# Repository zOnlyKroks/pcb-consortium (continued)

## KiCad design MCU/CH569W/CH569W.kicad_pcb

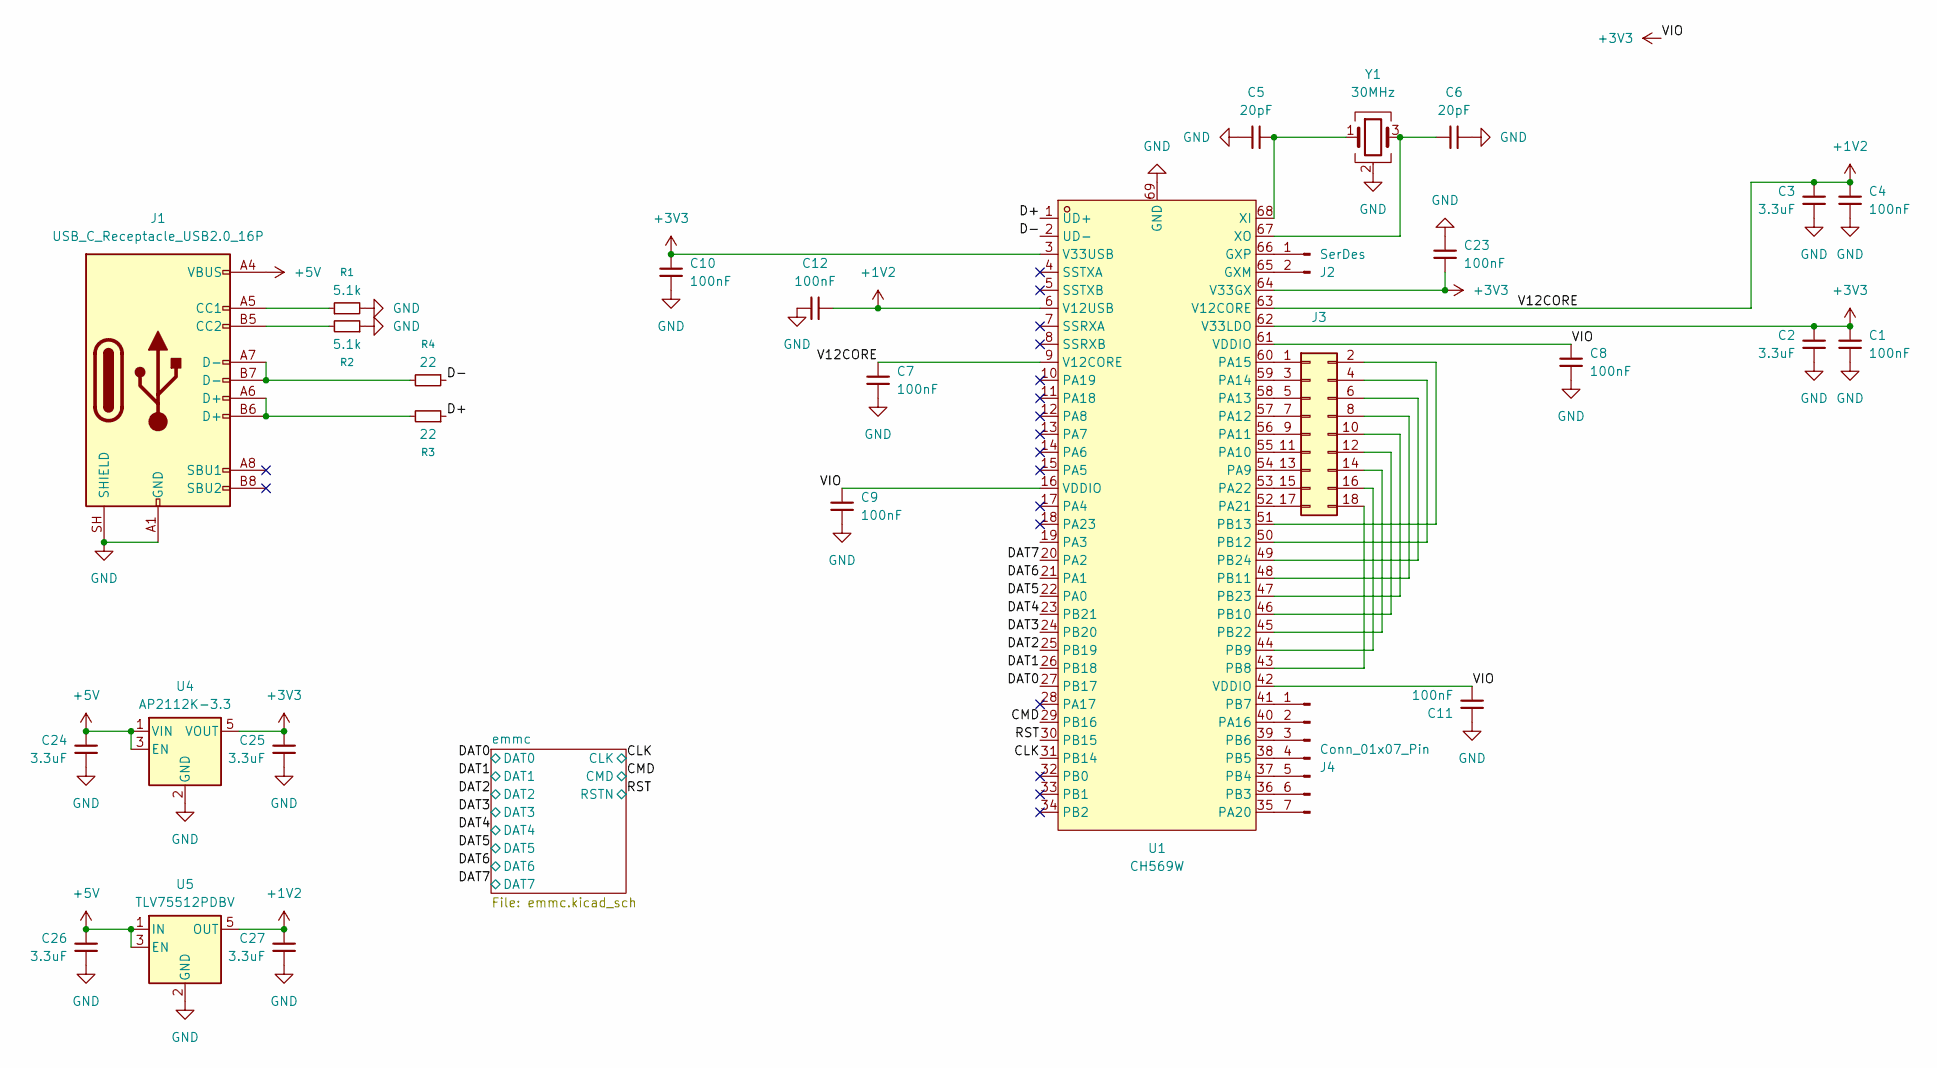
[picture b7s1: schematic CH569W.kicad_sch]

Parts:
C1, C4, C7, C8, C9, C10, C11, C12, C23: 100nF; C_0603_1608Metric
C2, C3, C24, C25, C26, C27: 3.3uF; C_0603_1608Metric
C5, C6: 20pF; C_0603_1608Metric
J1: USB_C_Receptacle_USB2.0_16P; USB_C_Receptacle_HRO_TYPE-C-31-M-12
J2: SerDes; PinHeader_1x02_P2.54mm_Vertical
J3: Conn_02x09_Odd_Even; PinHeader_2x09_P2.54mm_Vertical
J4: Conn_01x07_Pin; PinHeader_1x07_P2.54mm_Vertical
R1, R2: 5.1k; R_0603_1608Metric
R3, R4: 22; R_0603_1608Metric
U1: CH569W; MPN CH569W; LCSC Part C2857462
U4: AP2112K-3.3; SOT-23-5
U5: TLV75512PDBV; SOT-23-5
Y1: 30MHz; Crystal_SMD_3225-4Pin_3.2x2.5mm

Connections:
+1V2: C3.1, C4.1, C7.1, C12.2, C27.1, U1.6 (V12USB), U1.9 (V12CORE), U1.63 (V12CORE), U5.5 (OUT)
+3V3: C1.1, C2.1, C8.1, C9.1, C10.1, C11.2, C23.2, C25.1, U1.3 (V33USB), U1.16 (VDDIO), U1.42 (VDDIO), U1.61 (VDDIO), U1.62 (V33LDO), U1.64 (V33GX), U4.5 (VOUT); also elsewhere on the board
+5V: C24.1, C26.1, J1.A4 (VBUS), J1.A9 (VBUS), J1.B4 (VBUS), J1.B9 (VBUS), U4.1 (VIN), U4.3 (EN), U5.1 (IN), U5.3 (EN)
/CLK: U1.31 (PB14); also elsewhere on the board
/CMD: U1.29 (PB16); also elsewhere on the board
/D+: R3.1, U1.1 (UD+)
/D-: R4.1, U1.2 (UD-)
/DAT0: U1.27 (PB17); also elsewhere on the board
/DAT1: U1.26 (PB18); also elsewhere on the board
/DAT2: U1.25 (PB19); also elsewhere on the board
/DAT3: U1.24 (PB20); also elsewhere on the board
/DAT4: U1.23 (PB21); also elsewhere on the board
/DAT5: U1.22 (PA0); also elsewhere on the board
/DAT6: U1.21 (PA1); also elsewhere on the board
/DAT7: U1.20 (PA2); also elsewhere on the board
/RST: U1.30 (PB15); also elsewhere on the board
GND: C1.2, C2.2, C3.2, C4.2, C5.1, C6.2, C7.2, C8.2, C9.2, C10.2, C11.1, C12.1, C23.1, C24.2, C25.2, C26.2, C27.2, J1.A1 (GND), J1.A12 (GND), J1.B1 (GND), J1.B12 (GND), J1.SH (SHIELD), R1.2, R2.1, U1.69 (GND), U4.2 (GND), U5.2 (GND), Y1.2 (G), Y1.4 (G); also elsewhere on the board
unnamed: J1.A5 (CC1), R1.1
unnamed: J1.B5 (CC2), R2.2
unnamed: J1.A6 (D+), J1.B6 (D+), R3.2
unnamed: J1.A7 (D-), J1.B7 (D-), R4.2
unnamed: J2.1, U1.66 (GXP)
unnamed: J2.2, U1.65 (GXM)
unnamed: J3.1, U1.60 (PA15)
unnamed: J3.2, U1.51 (PB13)
unnamed: J3.3, U1.59 (PA14)
unnamed: J3.4, U1.50 (PB12)
unnamed: J3.5, U1.58 (PA13)
unnamed: J3.6, U1.49 (PB24)
unnamed: J3.7, U1.57 (PA12)
unnamed: J3.8, U1.48 (PB11)
unnamed: J3.9, U1.56 (PA11)
unnamed: J3.10, U1.47 (PB23)
unnamed: J3.11, U1.55 (PA10)
unnamed: J3.12, U1.46 (PB10)
unnamed: J3.13, U1.54 (PA9)
unnamed: J3.14, U1.45 (PB22)
unnamed: J3.15, U1.53 (PA22)
unnamed: J3.16, U1.44 (PB9)
unnamed: J3.17, U1.52 (PA21)
unnamed: J3.18, U1.43 (PB8)
unnamed: J4.1, U1.41 (PB7)
unnamed: J4.2, U1.40 (PA16)
unnamed: J4.3, U1.39 (PB6)
unnamed: J4.4, U1.38 (PB5)
unnamed: J4.5, U1.37 (PB4)
unnamed: J4.6, U1.36 (PB3)
unnamed: J4.7, U1.35 (PA20)
unnamed: C5.2, U1.68 (XI), Y1.1
unnamed: C6.1, U1.67 (XO), Y1.3

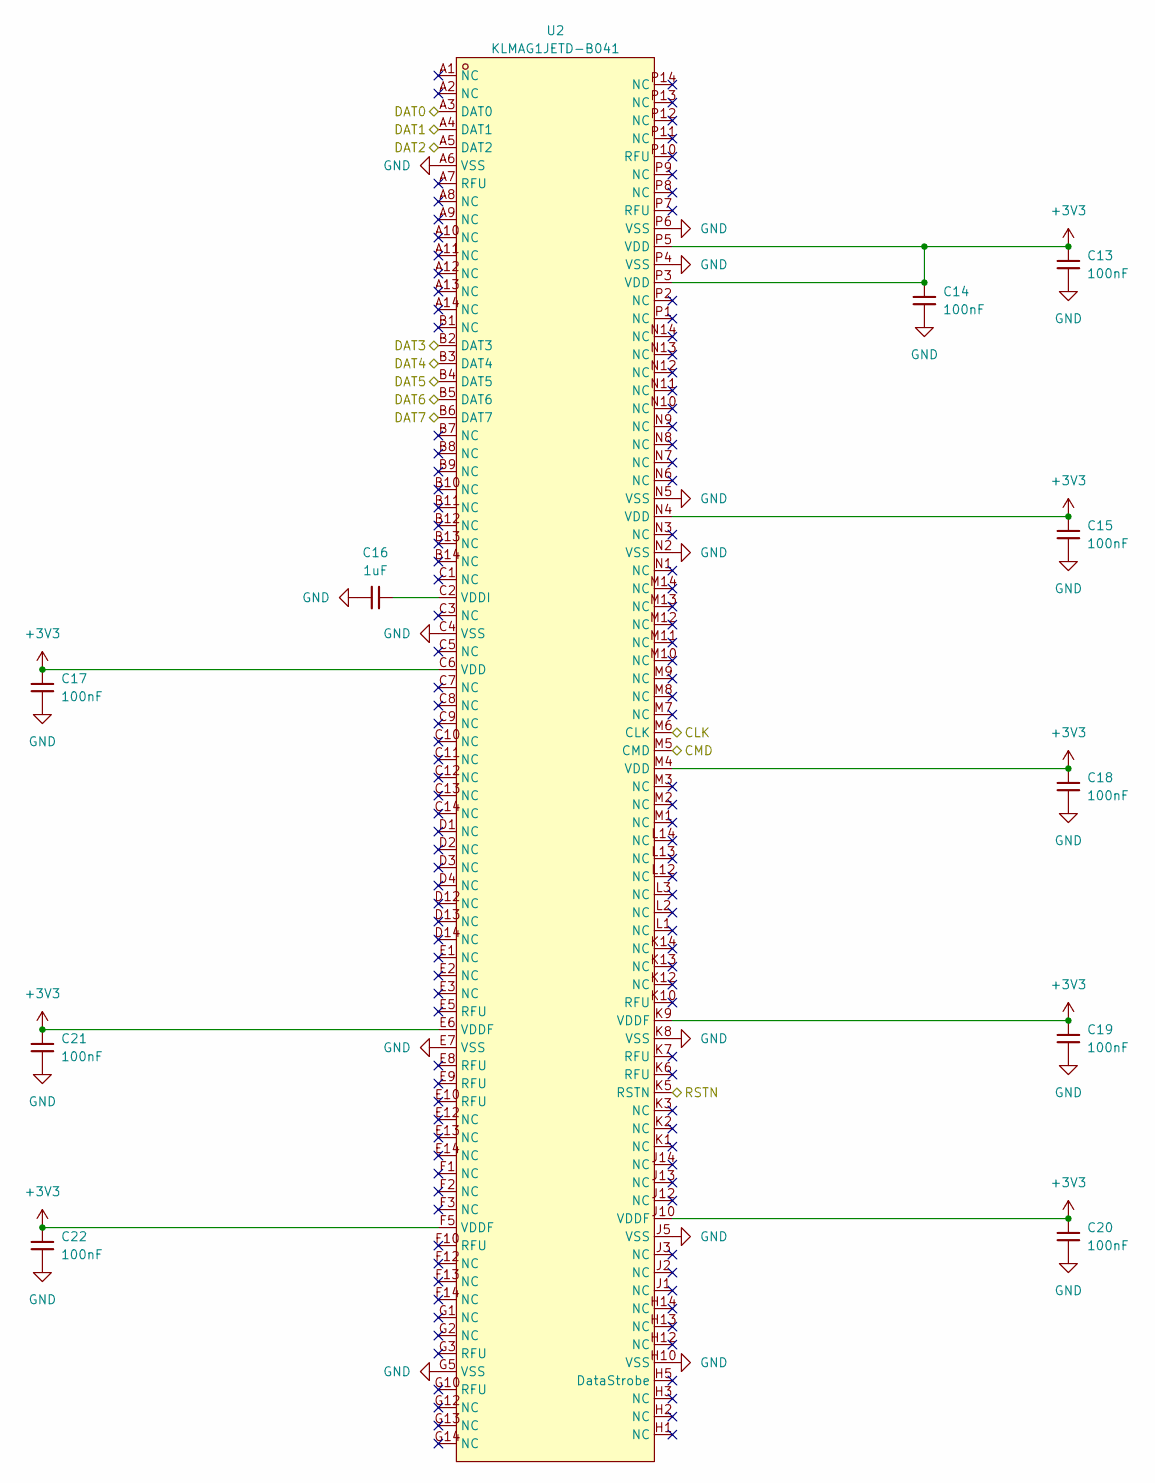
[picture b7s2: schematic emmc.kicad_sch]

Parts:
C13, C14, C15, C17, C18, C19, C20, C21, C22: 100nF; C_0603_1608Metric
C16: 1uF; C_0603_1608Metric
U2: KLMAG1JETD-B041; MPN KLMAG1JETD-B041; LCSC Part C499919

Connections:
+3V3: C13.1, C14.1, C15.1, C17.1, C18.1, C19.1, C20.1, C21.1, C22.1, U2.C6 (VDD), U2.E6 (VDDF), U2.F5 (VDDF), U2.J10 (VDDF), U2.K9 (VDDF), U2.M4 (VDD), U2.N4 (VDD), U2.P3 (VDD), U2.P5 (VDD); also elsewhere on the board
/CLK: U2.M6 (CLK); also elsewhere on the board
/CMD: U2.M5 (CMD); also elsewhere on the board
/DAT0: U2.A3 (DAT0); also elsewhere on the board
/DAT1: U2.A4 (DAT1); also elsewhere on the board
/DAT2: U2.A5 (DAT2); also elsewhere on the board
/DAT3: U2.B2 (DAT3); also elsewhere on the board
/DAT4: U2.B3 (DAT4); also elsewhere on the board
/DAT5: U2.B4 (DAT5); also elsewhere on the board
/DAT6: U2.B5 (DAT6); also elsewhere on the board
/DAT7: U2.B6 (DAT7); also elsewhere on the board
/RST: U2.K5 (RSTN); also elsewhere on the board
GND: C13.2, C14.2, C15.2, C16.1, C17.2, C18.2, C19.2, C20.2, C21.2, C22.2, U2.A6 (VSS), U2.C4 (VSS), U2.E7 (VSS), U2.G5 (VSS), U2.H10 (VSS), U2.J5 (VSS), U2.K8 (VSS), U2.N2 (VSS), U2.N5 (VSS), U2.P4 (VSS), U2.P6 (VSS); also elsewhere on the board
unnamed: C16.2, U2.C2 (VDDI)

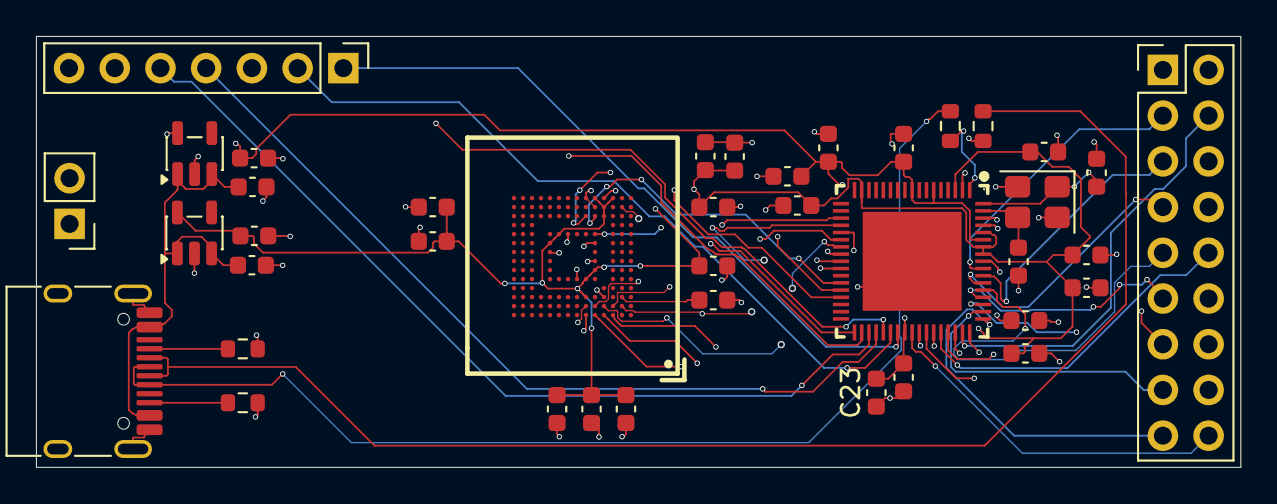
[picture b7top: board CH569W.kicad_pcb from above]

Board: 4 copper layers, 66.9 x 23.9 mm, 40 parts (0 on the bottom side), 51 nets.

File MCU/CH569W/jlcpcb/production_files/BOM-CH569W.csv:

Comment,Designator,Footprint,LCSC,Quantity
CH569W,U1,CH569W,C2857462,1
KLMAG1JETD-B041,U2,KLMAG1JETD-B041,C499919,1
5.1k,R2,R_0603_1608Metric,,1
3.3uF,C3,C_0603_1608Metric,,1
3.3uF,C2,C_0603_1608Metric,,1
100nF,C21,C_0603_1608Metric,,1
USB_C_Receptacle_USB2.0_16P,J1,USB_C_Receptacle_HRO_TYPE-C-31-M-12,,1
20pF,C6,C_0603_1608Metric,,1
20pF,C5,C_0603_1608Metric,,1
Conn_02x09_Odd_Even,J3,PinHeader_2x09_P2.54mm_Vertical,,1
100nF,C23,C_0603_1608Metric,,1
100nF,C22,C_0603_1608Metric,,1
Conn_01x07_Pin,J4,PinHeader_1x07_P2.54mm_Vertical,,1
100nF,C7,C_0603_1608Metric,,1
100nF,C9,C_0603_1608Metric,,1
100nF,C4,C_0603_1608Metric,,1
100nF,C13,C_0603_1608Metric,,1
30MHz,Y1,Crystal_SMD_3225-4Pin_3.2x2.5mm,,1
100nF,C14,C_0603_1608Metric,,1
22,R4,R_0603_1608Metric,,1
3.3uF,C25,C_0603_1608Metric,,1
100nF,C12,C_0603_1608Metric,,1
AP2112K-3.3,U4,SOT-23-5,,1
3.3uF,C24,C_0603_1608Metric,,1
3.3uF,C27,C_0603_1608Metric,,1
100nF,C20,C_0603_1608Metric,,1
100nF,C10,C_0603_1608Metric,,1
1uF,C16,C_0603_1608Metric,,1
22,R3,R_0603_1608Metric,,1
100nF,C19,C_0603_1608Metric,,1
100nF,C17,C_0603_1608Metric,,1
100nF,C18,C_0603_1608Metric,,1
100nF,C8,C_0603_1608Metric,,1
TLV75512PDBV,U5,SOT-23-5,,1
100nF,C1,C_0603_1608Metric,,1
5.1k,R1,R_0603_1608Metric,,1
3.3uF,C26,C_0603_1608Metric,,1
SerDes,J2,PinHeader_1x02_P2.54mm_Vertical,,1
100nF,C11,C_0603_1608Metric,,1
100nF,C15,C_0603_1608Metric,,1

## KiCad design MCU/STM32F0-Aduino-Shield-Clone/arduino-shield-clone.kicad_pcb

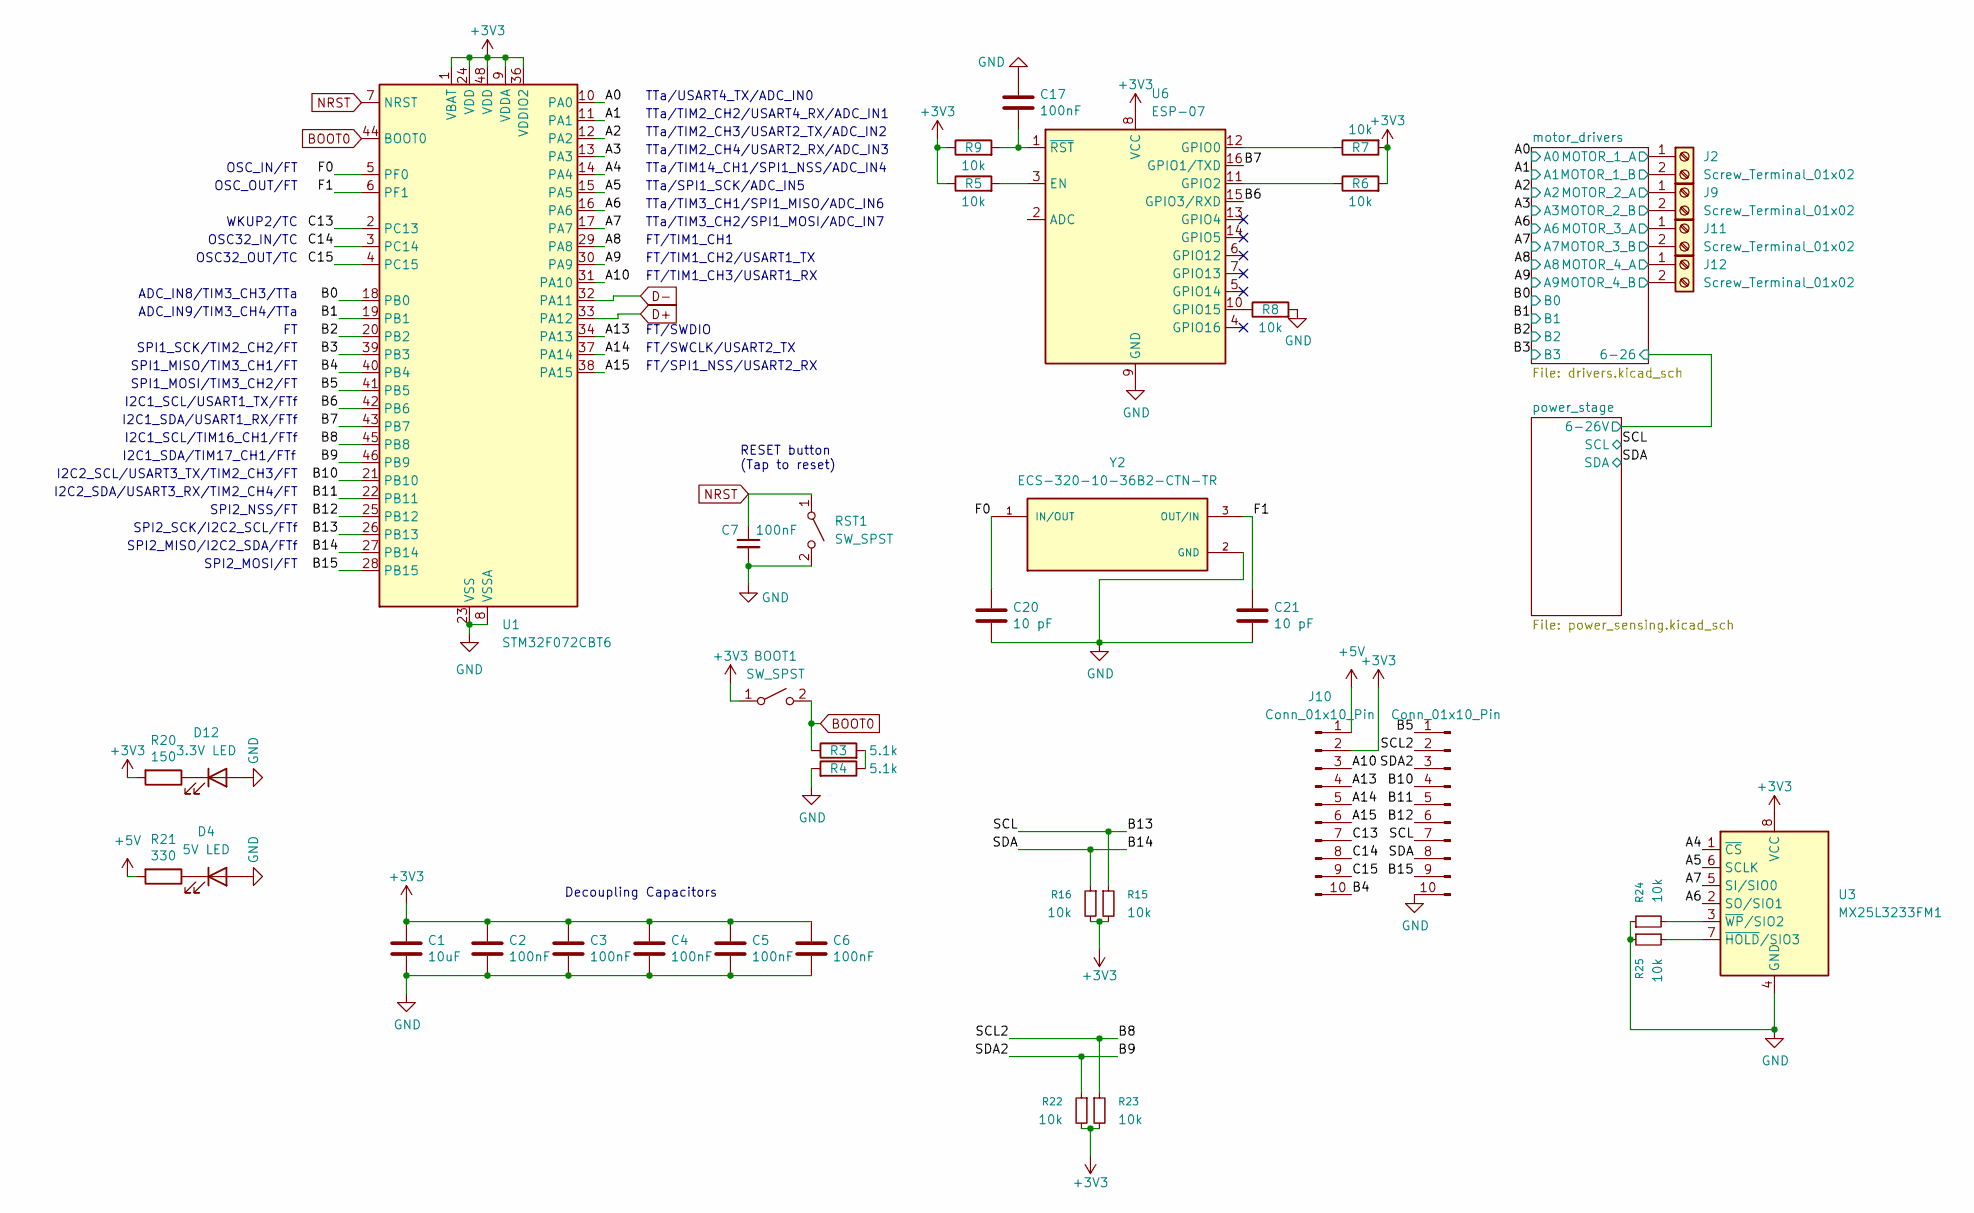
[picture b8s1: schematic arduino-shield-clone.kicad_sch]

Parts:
BOOT1: SW_SPST; SW_SPST_TL3342; LCSC Part # C2886897
C1: 10uF; C_0805_2012Metric; LCSC C307331
C2, C3, C4, C5, C6, C7, C17: 100nF; C_0805_2012Metric; LCSC C307331
C20, C21: 10 pF; C_0805_2012Metric; LCSC C307331
D4: 5V LED; LED_0805_2012Metric; LCSC Part # C98225
D12: 3.3V LED; LED_0805_2012Metric; LCSC Part # C98225
J2, J9, J11, J12: Screw_Terminal_01x02; TerminalBlock_Phoenix_MKDS-1,5-2-5.08_1x02_P5.08mm_Horizont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; LCSC Part # C5183929
J8, J10: Conn_01x10_Pin; PinHeader_1x10_P2.54mm_Vertical; LCSC Part # C42431810
R3, R4: 5.1k; R_0805_2012Metric
R5, R6, R7, R8, R9, R15, R16, R22, R23, R24, R25: 10k; R_0805_2012Metric; LCSC Part # C84376
R20: 150; R_0805_2012Metric; LCSC Part # C17471
R21: 330; R_0805_2012Metric; LCSC Part # C17630
RST1: SW_SPST; SW_SPST_TL3342; LCSC Part # C2886897
U1: STM32F072CBT6; LQFP-48_7x7mm_P0.5mm; JlcRotOffset 90
U3: MX25L3233FM1; JEITA_SOIC-8_3.9x4.9mm_P1.27mm; LCSC Part # C2802994
U6: ESP-07; LCSC Part # C82894
Y2: ECS-320-10-36B2-CTN-TR; XTAL_ECS-320-10-36B2-CTN-TR; PARTREV 2018; LCSC Part # C6239260

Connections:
+3V3: BOOT1.1 (A), C1.1, C2.1, C3.1, C4.1, C5.1, C6.1, J10.2, R5.1, R6.2, R7.2, R9.1, R15.2, R16.2, R20.2, R22.2, R23.2, U1.1 (VBAT), U1.9 (VDDA), U1.24 (VDD), U1.36 (VDDIO2), U1.48 (VDD), U3.8 (VCC), U6.8 (VCC); also elsewhere on the board
+5V: J10.1, R21.2; also elsewhere on the board
/A0: U1.10 (PA0); also elsewhere on the board
/A1: U1.11 (PA1); also elsewhere on the board
/A2: U1.12 (PA2); also elsewhere on the board
/A3: U1.13 (PA3); also elsewhere on the board
/A4: U1.14 (PA4), U3.1 (~CS)
/A5: U1.15 (PA5), U3.6 (SCLK)
/A6: U1.16 (PA6), U3.2 (SO/SIO1); also elsewhere on the board
/A7: U1.17 (PA7), U3.5 (SI/SIO0); also elsewhere on the board
/A8: U1.29 (PA8); also elsewhere on the board
/A9: U1.30 (PA9); also elsewhere on the board
/A10: J10.3, U1.31 (PA10)
/A13: J10.4, U1.34 (PA13)
/A14: J10.5, U1.37 (PA14)
/A15: J10.6, U1.38 (PA15)
/B0: U1.18 (PB0); also elsewhere on the board
/B1: U1.19 (PB1); also elsewhere on the board
/B2: U1.20 (PB2); also elsewhere on the board
/B3: U1.39 (PB3); also elsewhere on the board
/B4: J10.10, U1.40 (PB4)
/B5: J8.1, U1.41 (PB5)
/B6: U1.42 (PB6), U6.15 (GPIO3/RXD)
/B7: U1.43 (PB7), U6.16 (GPIO1/TXD)
/B8: J8.2, R23.1, U1.45 (PB8)
/B9: J8.3, R22.1, U1.46 (PB9)
/B10: J8.4, U1.21 (PB10)
/B11: J8.5, U1.22 (PB11)
/B12: J8.6, U1.25 (PB12)
/B13: J8.7, R15.1, U1.26 (PB13)
/B14: J8.8, R16.1, U1.27 (PB14)
/B15: J8.9, U1.28 (PB15)
/C13: J10.7, U1.2 (PC13)
/C14: J10.8, U1.3 (PC14)
/C15: J10.9, U1.4 (PC15)
/F0: C20.1, U1.5 (PF0), Y2.1 (IN/OUT)
/F1: C21.1, U1.6 (PF1), Y2.3 (OUT/IN)
/motor_drivers/MOTOR_1_A: J2.1; also elsewhere on the board
/motor_drivers/MOTOR_1_B: J2.2; also elsewhere on the board
/motor_drivers/MOTOR_2_A: J9.1; also elsewhere on the board
/motor_drivers/MOTOR_2_B: J9.2; also elsewhere on the board
/motor_drivers/MOTOR_3_A: J11.1; also elsewhere on the board
/motor_drivers/MOTOR_3_B: J11.2; also elsewhere on the board
/motor_drivers/MOTOR_4_A: J12.1; also elsewhere on the board
/motor_drivers/MOTOR_4_B: J12.2; also elsewhere on the board
BOOT0: BOOT1.2 (B), R3.1, U1.44 (BOOT0)
D+: U1.33 (PA12); also elsewhere on the board
D-: U1.32 (PA11); also elsewhere on the board
GND: C1.2, C2.2, C3.2, C4.2, C5.2, C6.2, C7.2, C17.1, C20.2, C21.2, D4.2 (A), D12.2 (A), J8.10, R4.2, R8.2, R24.1, R25.1, RST1.2 (B), U1.8 (VSSA), U1.23 (VSS), U1.35 (VSS), U1.47 (VSS), U3.4 (GND), U6.9 (GND), Y2.2 (GND), Y2.4 (GND); also elsewhere on the board
NRST: C7.1, RST1.1 (A), U1.7 (NRST)
unnamed: D4.1 (K), R21.1
unnamed: D12.1 (K), R20.1
unnamed: R3.2, R4.1
unnamed: R25.2, U3.7 (~HOLD/SIO3)
unnamed: R24.2, U3.3 (~WP/SIO2)
unnamed: R5.2, U6.3 (EN)
unnamed: R7.1, U6.12 (GPIO0)
unnamed: R6.1, U6.11 (GPIO2)
unnamed: R8.1, U6.10 (GPIO15)
unnamed: C17.2, R9.2, U6.1 (~RST)

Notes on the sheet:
TTa/TIM14_CH1/SPI1_NSS/ADC_IN4
ADC_IN8/TIM3_CH3/TTa
FT/SWCLK/USART2_TX
Decoupling Capacitors
FT/TIM1_CH2/USART1_TX
TTa/USART4_TX/ADC_IN0
TTa/TIM3_CH2/SPI1_MOSI/ADC_IN7
TTa/TIM2_CH3/USART2_TX/ADC_IN2
FT/SPI1_NSS/USART2_RX
I2C1_SCL/TIM16_CH1/FTf
SPI1_MOSI/TIM3_CH2/FT
SPI1_SCK/TIM2_CH2/FT
WKUP2/TC
SPI2_MOSI/FT
RESET button (Tap to reset)
OSC32_IN/TC
FT/TIM1_CH3/USART1_RX
I2C1_SCL/USART1_TX/FTf
TTa/TIM2_CH2/USART4_RX/ADC_IN1
TTa/TIM2_CH4/USART2_RX/ADC_IN3
TTa/SPI1_SCK/ADC_IN5
ADC_IN9/TIM3_CH4/TTa
I2C2_SCL/USART3_TX/TIM2_CH3/FT
I2C1_SDA/TIM17_CH1/FTf
SPI2_NSS/FT
SPI1_MISO/TIM3_CH1/FT
TTa/TIM3_CH1/SPI1_MISO/ADC_IN6
OSC_IN/FT
OSC_OUT/FT
OSC32_OUT/TC
FT/TIM1_CH1
SPI2_SCK/I2C2_SCL/FTf
I2C1_SDA/USART1_RX/FTf
I2C2_SDA/USART3_RX/TIM2_CH4/FT
FT/SWDIO
SPI2_MISO/I2C2_SDA/FTf

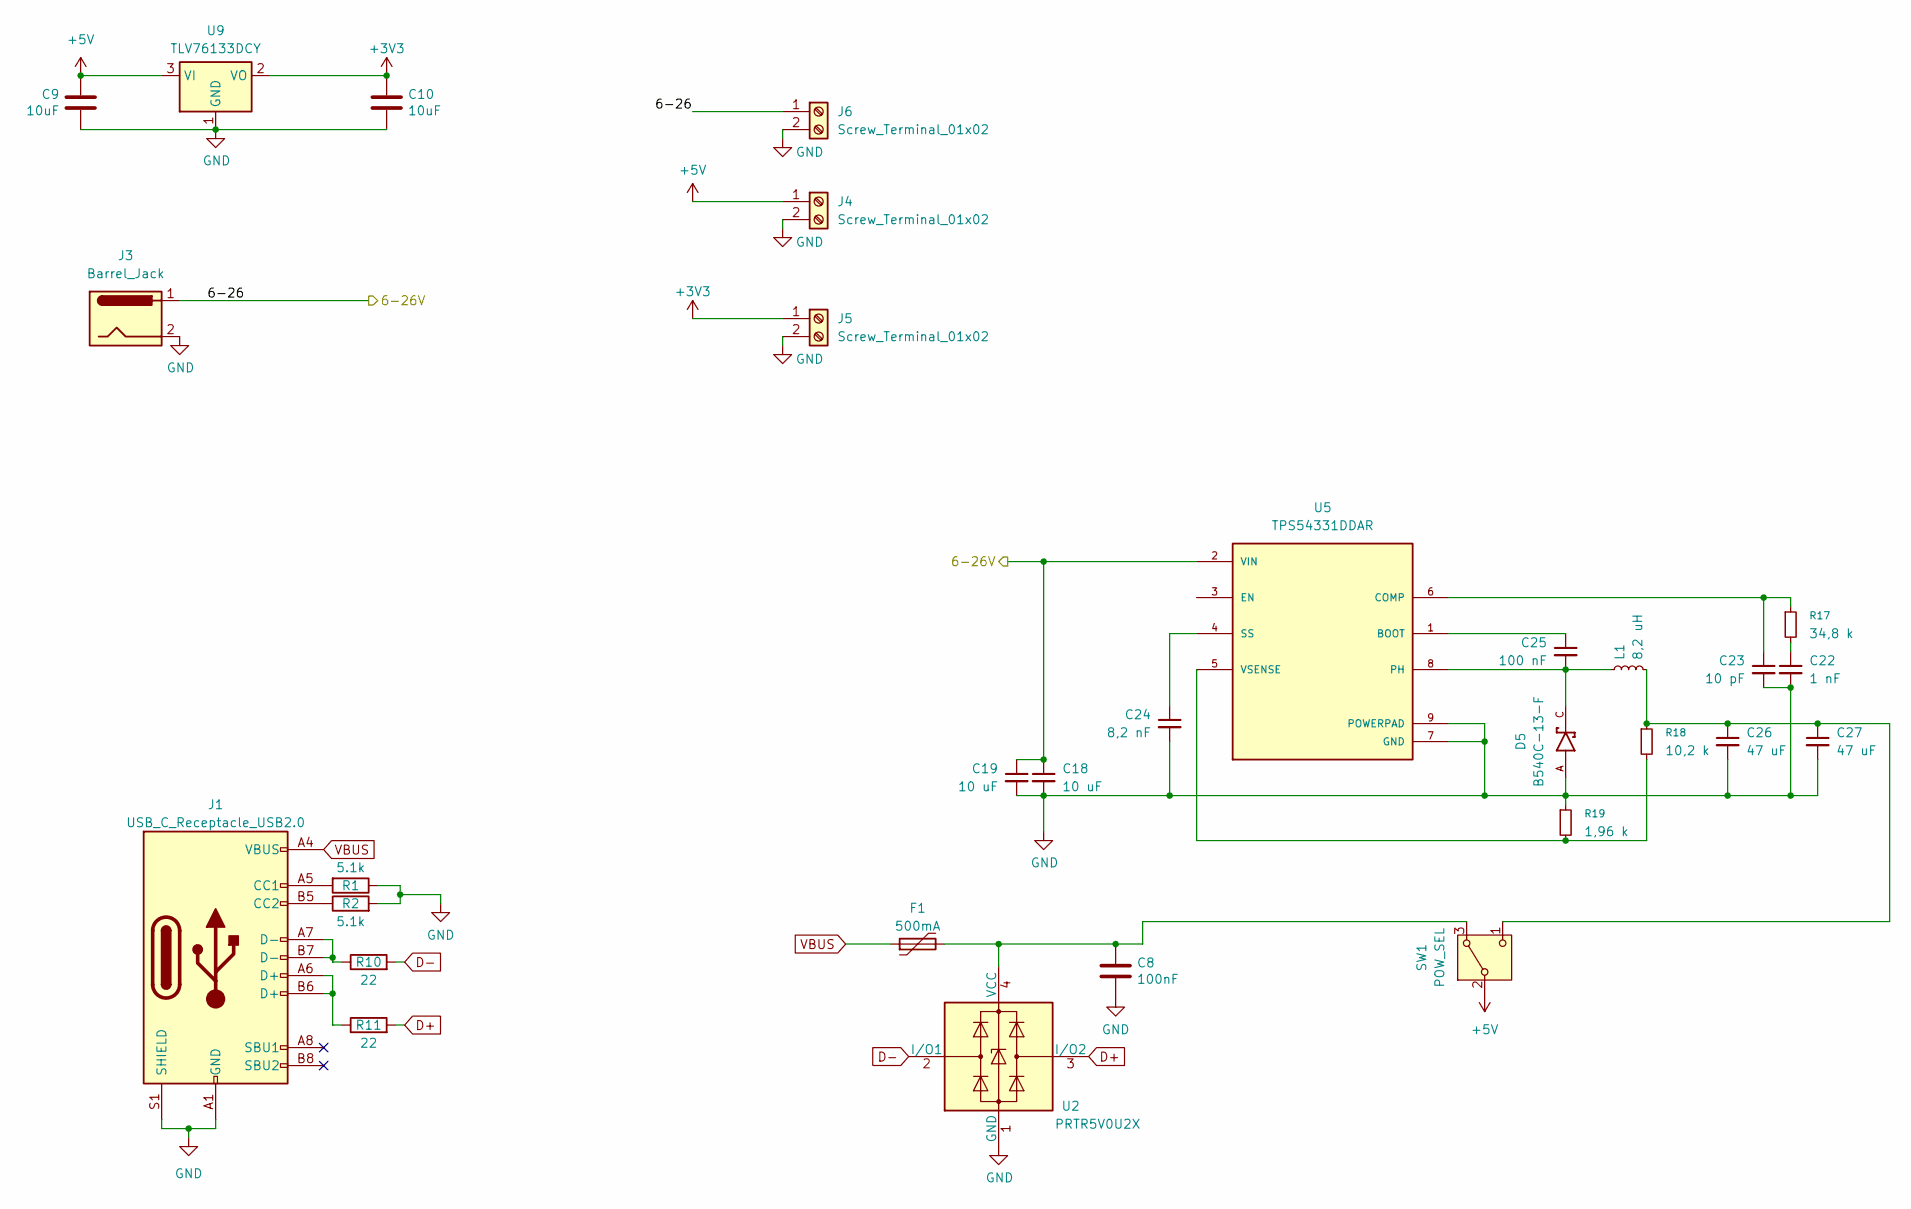
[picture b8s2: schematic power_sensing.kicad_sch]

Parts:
C8: 100nF; C_0805_2012Metric; LCSC C307331
C9, C10: 10uF; C_0805_2012Metric; LCSC C307331
C18, C19: 10 uF; C_1210_3225Metric; LCSC Part # C18739
C22: 1 nF; C_0805_2012Metric; LCSC Part # C1791
C23: 10 pF; C_0805_2012Metric; LCSC Part # C41361255
C24: 8,2 nF; C_0805_2012Metric; LCSC Part # C1758
C25: 100 nF; C_0805_2012Metric; LCSC Part # C710980
C26, C27: 47 uF; C_1210_3225Metric; LCSC Part # C3903983
D5: B540C-13-F; DIOM6959X245N; PARTREV V1.0; LCSC Part # C72264
F1: 500mA; Fuse_1206_3216Metric; LCSC C135341
J1: USB_C_Receptacle_USB2.0; USB_C_Receptacle_HRO_TYPE-C-31-M-12; JlcRotOffset 180
J3: Barrel_Jack; BarrelJack_Horizontal; LCSC Part # C319099
J4, J5, J6: Screw_Terminal_01x02; TerminalBlock_Phoenix_MKDS-1,5-2-5.08_1x02_P5.08mm_Horizont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; LCSC Part # C5183929
L1: 8,2 uH; IND_BOURNS_SDR1307; LCSC Part # C49672242
R1, R2: 5.1k; R_0805_2012Metric; LCSC Part # C2930296
R10, R11: 22; R_0805_2012Metric; LCSC Part # C107702
R17: 34,8 k; R_0805_2012Metric; LCSC Part # C2076772
R18: 10,2 k; R_0805_2012Metric; LCSC Part # C481923
R19: 1,96 k; R_0805_2012Metric; LCSC Part # C2092068
SW1: POW_SEL; Nidec_Copal_CAS-120A; LCSC Part # C5962834
U2: PRTR5V0U2X; SOT-143; LCSC C2827688
U5: TPS54331DDAR; CONV_TPS54331DDAR; PARTREV F; LCSC Part # C90761
U9: TLV76133DCY; SOT-223-3_TabPin2; LCSC Part # C7527500

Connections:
+3V3: C10.1, J5.1, U9.2 (VO); also elsewhere on the board
+5V: C9.1, J4.1, SW1.2 (B), U9.3 (VI); also elsewhere on the board
/power_stage/6-26: C18.1, C19.1, J3.1, J6.1, U5.2 (VIN); also elsewhere on the board
D+: R11.2, U2.3 (I/O2); also elsewhere on the board
D-: R10.2, U2.2 (I/O1); also elsewhere on the board
GND: C8.2, C9.2, C10.2, C18.2, C19.2, C22.2, C23.2, C24.2, C26.2, C27.2, D5.A, J1.A1 (GND), J1.A12 (GND), J1.B1 (GND), J1.B12 (GND), J1.S1 (SHIELD), J3.2, J4.2, J5.2, J6.2, R1.1, R2.2, R19.1, U2.1 (GND), U5.7 (GND), U5.9 (POWERPAD), U9.1 (GND); also elsewhere on the board
unnamed: C22.1, R17.2
unnamed: J1.A5 (CC1), R1.2
unnamed: J1.B5 (CC2), R2.1
unnamed: J1.A6 (D+), J1.B6 (D+), R11.1
unnamed: J1.A7 (D-), J1.B7 (D-), R10.1
unnamed: C8.1, F1.2, SW1.3 (A), U2.4 (VCC)
unnamed: C26.1, C27.1, L1.2, R18.1, SW1.1 (C)
unnamed: C25.1, U5.1 (BOOT)
unnamed: C23.1, R17.1, U5.6 (COMP)
unnamed: C25.2, D5.C, L1.1, U5.8 (PH)
unnamed: C24.1, U5.4 (SS)
unnamed: R18.2, R19.2, U5.5 (VSENSE)
VBUS: F1.1, J1.A4 (VBUS), J1.A9 (VBUS), J1.B4 (VBUS), J1.B9 (VBUS)

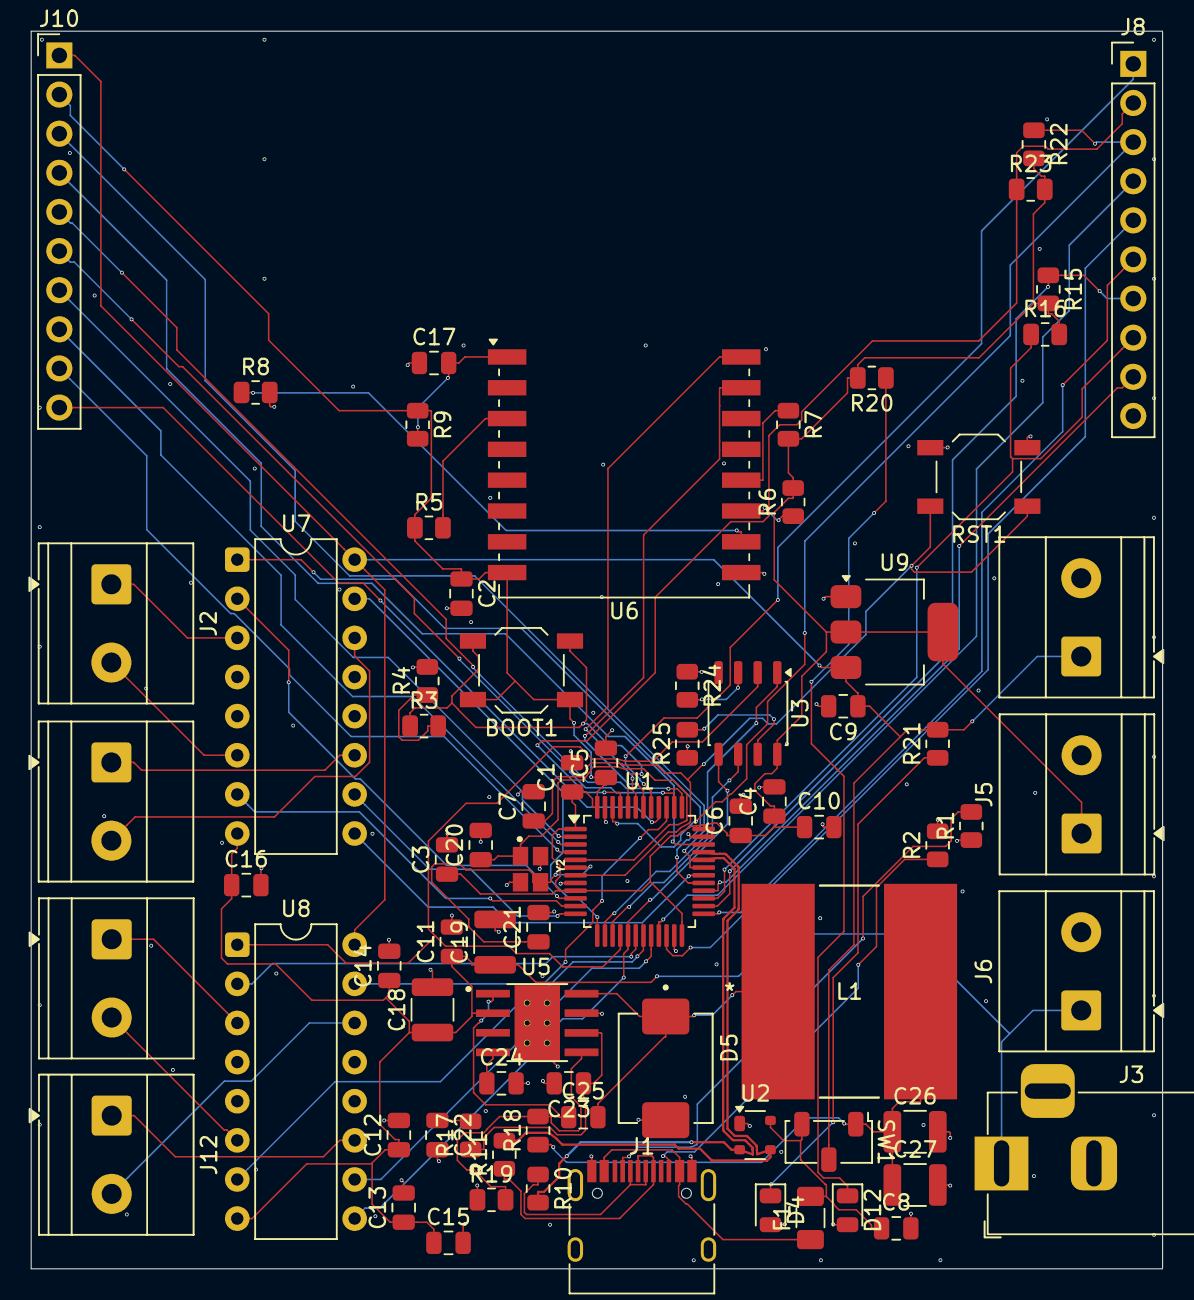
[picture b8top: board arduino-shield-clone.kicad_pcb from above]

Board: 4 copper layers, 73.4 x 80.4 mm, 77 parts (0 on the bottom side), 74 nets.

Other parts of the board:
C11: 100uF; C_0805_2012Metric
C12, C13, C14, C15, C16: 100nF; C_0805_2012Metric
U7, U8: L293D; DIP-16_W7.62mm

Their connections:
+5V: U7.16 (VCC1), U8.16 (VCC1); also elsewhere on the board
/A0: U7.2 (1A); also elsewhere on the board
/A1: U7.7 (2A); also elsewhere on the board
/A2: U7.10 (3A); also elsewhere on the board
/A3: U7.15 (4A); also elsewhere on the board
/A6: U8.1 (EN1,2); also elsewhere on the board
/A7: U8.9 (EN3,4); also elsewhere on the board
/A8: U7.1 (EN1,2); also elsewhere on the board
/A9: U7.9 (EN3,4); also elsewhere on the board
/B0: U8.2 (1A); also elsewhere on the board
/B1: U8.7 (2A); also elsewhere on the board
/B2: U8.10 (3A); also elsewhere on the board
/B3: U8.15 (4A); also elsewhere on the board
/motor_drivers/MOTOR_1_A: U7.3 (1Y); also elsewhere on the board
/motor_drivers/MOTOR_1_B: U7.6 (2Y); also elsewhere on the board
/motor_drivers/MOTOR_2_A: U7.11 (3Y); also elsewhere on the board
/motor_drivers/MOTOR_2_B: U7.14 (4Y); also elsewhere on the board
/motor_drivers/MOTOR_3_A: U8.3 (1Y); also elsewhere on the board
/motor_drivers/MOTOR_3_B: U8.6 (2Y); also elsewhere on the board
/motor_drivers/MOTOR_4_A: U8.11 (3Y); also elsewhere on the board
/motor_drivers/MOTOR_4_B: U8.14 (4Y); also elsewhere on the board
/power_stage/6-26: C11.1, C12.1, C13.1, C14.1, C15.1, C16.1, U7.8 (VCC2), U8.8 (VCC2); also elsewhere on the board
GND: C11.2, C12.2, C13.2, C14.2, C15.2, C16.2, U7.4 (GND), U7.5 (GND), U7.12 (GND), U7.13 (GND), U8.4 (GND), U8.5 (GND), U8.12 (GND), U8.13 (GND); also elsewhere on the board

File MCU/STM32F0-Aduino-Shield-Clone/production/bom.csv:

Designator,Footprint,Quantity,Value,LCSC Part #
"BOOT1, RST1",SW_SPST_TL3342,2,SW_SPST,C2886897
"C1, C10, C9",0805,3,10uF,C307331
C11,0805,1,100uF,C307331
"C12, C13, C14, C15, C16, C17, C2, C3, C4, C5, C6, C7, C8",0805,13,100nF,C307331
"C18, C19",1210,2,10 uF,C18739
"C20, C21",0805,2,10 pF,C307331
C22,0805,1,1 nF,C1791
C23,0805,1,10 pF,C41361255
C24,0805,1,"8,2 nF",C1758
C25,0805,1,100 nF,C710980
"C26, C27",1210,2,47 uF,C3903983
D12,0805,1,3.3V LED,C98225
D4,0805,1,5V LED,C98225
D5,DIOM6959X245N,1,B540C-13-F,C72264
F1,1206,1,500mA,C135341
J1,USB_C_Receptacle_HRO_TYPE-C-31-M-12,1,USB_C_Receptacle_USB2.0,C165948
"J10, J8",PinHeader_1x10_P2.54mm_Vertical,2,Conn_01x10_Pin,C42431810
"J11, J12, J2, J4, J5, J6, J9","TerminalBlock_Phoenix_MKDS-1,5-2-5.08_1x02_P5.08mm_Horizontal",7,Screw_Terminal_01x02,C5183929
J3,BarrelJack_Horizontal,1,Barrel_Jack,C319099
L1,IND_BOURNS_SDR1307,1,"8,2 uH",C49672242
"R1, R2",0805,2,5.1k,C2930296
"R10, R11",0805,2,22,C107702
"R12, R13, R14",0805,3,0.01,C2903468
"R15, R16, R22, R23, R24, R25, R5, R6, R7, R8, R9",0805,11,10k,C84376
R17,0805,1,"34,8 k",C2076772
R18,0805,1,"10,2 k",C481923
R19,0805,1,"1,96 k",C2092068
R20,0805,1,150,C17471
R21,0805,1,330,C17630
"R3, R4",0805,2,5.1k,
SW1,Nidec_Copal_CAS-120A,1,POW_SEL,C5962834
U1,LQFP-48_7x7mm_P0.5mm,1,STM32F072CBT6,C81720
U2,SOT-143,1,PRTR5V0U2X,C2827688
U3,JEITA_SOIC-8_3.9x4.9mm_P1.27mm,1,MX25L3233FM1,C2802994
U4,Texas_RGV0016A_VQFN-16-1EP_4x4mm_P0.65mm_EP2.1x2.1mm,1,INA3221,C181255
U5,CONV_TPS54331DDAR,1,TPS54331DDAR,C90761
U6,ESP-07,1,ESP-07,C82894
"U7, U8",DIP-16_W7.62mm,2,L293D,C12340
U9,SOT-223-3_TabPin2,1,TLV76133DCY, C7527500
Y2,XTAL_ECS-320-10-36B2-CTN-TR,1,ECS-320-10-36B2-CTN-TR,C6239260
